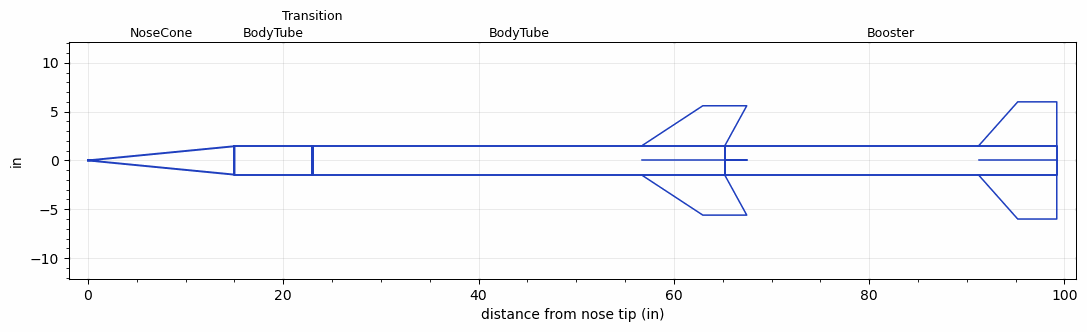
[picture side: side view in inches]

<RASAeroDocument>
 <FileVersion>2</FileVersion>
 <RocketDesign>
  <NoseCone>
   <Length>15</Length>
   <Diameter>2.91</Diameter>
   <Shape>Conical</Shape>
   <Location>0</Location>
  </NoseCone>
  <BodyTube>
   <Length>7.94</Length>
   <Diameter>2.91</Diameter>
   <Location>15</Location>
  </BodyTube>
  <Transition>
   <Length>0.078</Length>
   <Diameter>3</Diameter>
   <Location>22.94</Location>
   <RearDiameter>3</RearDiameter>
  </Transition>
  <BodyTube>
   <Length>42.195</Length>
   <Diameter>3</Diameter>
   <Location>23.018</Location>
   <Fin>
    <Count>4</Count>
    <Chord>8.5</Chord>
    <Span>4.1</Span>
    <SweepDistance>6.25</SweepDistance>
    <TipChord>4.5</TipChord>
    <Thickness>0.1875</Thickness>
    <LERadius>0.01</LERadius>
    <Location>8.5</Location>
    <AirfoilSection>Hexagonal</AirfoilSection>
    <FX1>0.5111</FX1>
    <FX3>0.5111</FX3>
   </Fin>
  </BodyTube>
  <Booster>
   <Length>34</Length>
   <Diameter>3</Diameter>
   <InsideDiameter>3</InsideDiameter>
   <RailGuideDiameter>0.2</RailGuideDiameter>
   <RailGuideHeight>0.025</RailGuideHeight>
   <Location>65.213</Location>
   <ShoulderLength>0</ShoulderLength>
   <Fin>
    <Count>4</Count>
    <Chord>8</Chord>
    <Span>4.5</Span>
    <SweepDistance>4</SweepDistance>
    <TipChord>4</TipChord>
    <Thickness>0.133</Thickness>
    <LERadius>0.01</LERadius>
    <Location>8</Location>
    <AirfoilSection>Hexagonal</AirfoilSection>
    <FX1>0.36</FX1>
    <FX3>0.36</FX3>
   </Fin>
  </Booster>
  <Surface>Rough Camouflage Paint</Surface>
  <ModifiedBarrowman>True</ModifiedBarrowman>
  <Turbulence>True</Turbulence>
  <UseBooster1>False</UseBooster1>
  <UseBooster2>False</UseBooster2>
 </RocketDesign>
 <LaunchSite>
  <Altitude>2000</Altitude>
  <Pressure>29.92</Pressure>
  <RodAngle>1</RodAngle>
  <RodLength>20</RodLength>
  <Temperature>80</Temperature>
  <WindSpeed>5</WindSpeed>
 </LaunchSite>
 <Recovery>
  <Altitude1>1000</Altitude1>
  <Altitude2>1000</Altitude2>
  <DeviceType1>None</DeviceType1>
  <DeviceType2>None</DeviceType2>
  <Event1>False</Event1>
  <Event2>False</Event2>
  <Size1>1</Size1>
  <Size2>1</Size2>
  <EventType1>None</EventType1>
  <EventType2>None</EventType2>
  <CD1>1.33</CD1>
  <CD2>1.33</CD2>
 </Recovery>
 <SimulationList>
  <Simulation>
   <SustainerEngine>N3051  (TsKrush)</SustainerEngine>
   <SustainerLaunchWt>22.67</SustainerLaunchWt>
   <SustainerNozzleDiameter>2.5</SustainerNozzleDiameter>
   <SustainerCG>43</SustainerCG>
   <SustainerIgnitionDelay>8</SustainerIgnitionDelay>
   <Booster1Engine>M1988  (TsKrush)</Booster1Engine>
   <Booster1LaunchWt>35.5</Booster1LaunchWt>
   <Booster1SeparationDelay>0</Booster1SeparationDelay>
   <Booster1IgnitionDelay>0</Booster1IgnitionDelay>
   <Booster1CG>58.5</Booster1CG>
   <Booster1NozzleDiameter>2.75</Booster1NozzleDiameter>
   <IncludeBooster1>True</IncludeBooster1>
   <Booster2Delay>0</Booster2Delay>
   <IncludeBooster2>False</IncludeBooster2>
   <TimetoApogee>65.55547</TimetoApogee>
   <MaxAltitude>72019.71</MaxAltitude>
   <MaxVelocity>4198.721</MaxVelocity>
  </Simulation>
 </SimulationList>
</RASAeroDocument>
